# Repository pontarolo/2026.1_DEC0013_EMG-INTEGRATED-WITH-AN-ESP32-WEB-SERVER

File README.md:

<div align="center">

<h4 align="center">Electromyograph integrated with an ESP32 Web Server</h4>

</div>

<p align="center">
  <a href="#materials">Materials</a> •
  <a href="#diagrams">Diagrams</a> •
  <a href="software/README.md">Software</a> •
  <a href="LICENSE">License</a>
</p>

---

## Basic Overview

This project consists of an implementation of a circuit to measure specific muscle activity, consisting of two channels, which means that it is possible to measure two muscles simultaneously. The project emerges as a way to detect muscular issues and restraints in a low-cost and reliable manner. The general architecture of this project is a connection between the electromyograph PCB and the ESP32 microcontroller, where the ESP32 acts as a web server with an WebSocket to handle the data plotting. The GIF shown above was made from a video of the electromyograph in operation, which recorded the web page hosted by the ESP32.

## Goals

| Type | Goal |
| :--- | :--- |
| **Hardware** | Design a circuit that is capable of effectively measuring muscle voltage |
| **Hardware** | Make the circuit as noise-free as possible |
| **Software** | Write an optimized code that can display, in real time, the muscle data |

### Project Directory Structure

```text
├── hardware/             # PCB design files (symbols, footprints, models, and Gerbers)
│   ├── footprints/       # Custom component footprints (.kicad_mod)
│   ├── kicad_files/      # KiCad project files and manufacturing Gerbers
│   ├── models/           # 3D step files for components
│   └── symbols/          # Custom schematic symbol libraries (.kicad_sym)
├── images/               # Visual assets for documentation and tutorials
└── software/             # Firmware and source code for the project
    └── plot/             # ESP32 source code for data acquisition
```

## Description

This section explains the details of the project, including the materials and tools used, communication and electrical diagrams and examples of its functionality.

###  Materials

<table>
  <tr>
    <td align="center" valign="top" width="150" style="border: none;">
      <br>
      <strong>Resistor</strong><br>
      <font color="#666" size="2">2x 220Ω • 1/4 W • 5% • THT</font>
    </td>
    <td align="center" valign="top" width="150" style="border: none;">
      <br>
      <strong>Resistor</strong><br>
      <font color="#666" size="2">4x 100KΩ • 1/4 W • 5% • THT</font>
    </td>
    <td align="center" valign="top" width="150" style="border: none;">
      <br>
      <strong>Resistor</strong><br>
      <font color="#666" size="2">4x 220KΩ • 1/4 W • 5% • THT</font>
    </td>
    <td align="center" valign="top" width="150" style="border: none;">
      <br>
      <strong>Trimpot</strong><br>
      <font color="#666" size="2">1x 10KΩ • THT</font>
    </td>
  </tr>
  <tr>
    <td align="center" valign="top" width="150" style="border: none;">
      <br>
      <strong>Capacitor</strong><br>
      <font color="#666" size="2">2x 100μF • Electrolytic • THT</font>
    </td>
    <td align="center" valign="top" width="150" style="border: none;">
      <br>
      <strong>Capacitor</strong><br>
      <font color="#666" size="2">2x 220nF • Ceramic • THT</font>
    </td>
    <td align="center" valign="top" width="150" style="border: none;">
      <br>
      <strong>Battery</strong><br>
      <font color="#666" size="2">2x Lithium-Ion • 3.7V • 18650</font>
    </td>
    <td align="center" valign="top" width="150" style="border: none;">
      <br>
      <strong>MT3608</strong><br>
      <font color="#666" size="2">1x Module</font>
    </td>
  </tr>
  <tr>
    <td align="center" valign="top" width="150" style="border: none;">
      <br>
      <strong>TP4056</strong><br>
      <font color="#666" size="2">1x Module</font>
    </td>
    <td align="center" valign="top" width="150" style="border: none;">
      <br>
      <strong>LM324N</strong><br>
      <font color="#666" size="2">1x Integrated Circuit</font>
    </td>
    <td align="center" valign="top" width="150" style="border: none;">
      <br>
      <strong>TRRS Breakout</strong><br>
      <font color="#666" size="2">1x Module</font>
    </td>
    <td align="center" valign="top" width="150" style="border: none;">
      <br>
      <strong>ESP32</strong><br>
      <font color="#666" size="2">1x ESP-WROOM-32</font>
    </td>
  </tr>
  <tr>
    <td align="center" valign="top" width="150" style="border: none;">
      <br>
      <strong>Isopropanol</strong><br>
      <font color="#666" size="2">1x 99.8% Pure</font>
    </td>
    <td align="center" valign="top" width="150" style="border: none;">
      <br>
      <strong>Cell Holder</strong><br>
      <font color="#666" size="2">1x Lithium-Ion • 18650 • Single</font>
    </td>
    <td align="center" valign="top" width="150" style="border: none;">
      <br>
      <strong>EMG Cable</strong><br>
      <font color="#666" size="2">2x P2 Connection</font>
    </td>
    <td align="center" valign="top" width="150" style="border: none;">
      <br>
      <strong>Electrodes</strong><br>
      <font color="#666" size="2">6x Disposable</font>
    </td>
  </tr>
</table>

###  Communication Diagram

In this subsection we will discuss the communication diagram of the project to give a general view of the signal path and a clearer understanding of the circuit itself.

The image above represents the communication diagram, which shows the signal path throughout the whole project. The user's noisy low-voltage signal is sent to the printed circuit board (PCB) through silver $Ag$ or silver chloride $AgCl$ electrodes, where it can be properly filtered and amplified. Then the clean signal is carried to the ESP32 microcontroller that acts as a WebSocket Server to handle massive data plotting, hosting an HTML page that displays the graph.

---

###  Electrical Diagram

In this subsection we will discuss the communication diagram of the project to give a general view of the signal processing and a clearer understanding of the circuit itself.

The image above represents the electrical diagram, which shows the electrical connection between the components. As shown in the image, the circuit consists of:

| Component | Role in the circuit |
| :--- | :--- |
| **Resistors** | Set the gain stages, establish amplifier feedback loops, and stabilize signal lines. |
| **Trimpot** | Adjusts the virtual ground offset (reference voltage) to bias the EMG signal for the ESP32 ADC. |
| **Capacitors** | Filter out DC offsets (high-pass) and high-frequency noise (low-pass), and decouple power rails. |
| **Battery** | Provides clean, isolated 3.7V power to eliminate grid noise ($60\text{ Hz}$) and ensure user safety. |
| **MT3608** | Boosts the 3.7V battery to a stable 5V, ensuring full dynamic range for the op-amps. |
| **TP4056** | Handles safe Li-Ion battery charging and provides over-discharge protection. |
| **LM324N** | Handles differential amplification and active filtering of the microvolt-level muscle signals. |
| **TRRS Breakout** | Serves as the input jack for the 3-lead electrode cable (Signal +, Signal -, and Reference). |
| **ESP32 (Implicit)** | Samples the analog processed signal and hosts the WebSocket server for real-time live plotting. |

To secure the right voltage for the ESP32 ADC pins, a set of calculations were made, using the following equations:

- **Op-Amps:** By applying Kirchhoff's Laws, it is possible to obtain the expressions for Common and Differential Mode Gain:

| Name | Equation |
| :--- | :--- |
| **Common Mode Voltage** | $V_{cm} = \frac{V_{electrode(+)} + V_{electrode(-)}}{2}$ |
| **Common Mode Gain** | $A_{cm} = 1 - \frac{R_4}{Z_1}$ |
| **Differential Mode Voltage** | $V_{dif} = V_{electrode(+)} - V_{electrode(-)}$ |
| **Differential Mode Gain** | $A_{dif} = -\left(\frac{1}{2} + \frac{R_4}{R_5} + \frac{2R_4}{Z_3} + \frac{R_4}{2Z_1}\right)$ |

Where the complex impedances $Z_1$ and $Z_3$ are defined in the frequency domain ($s$-domain) as:

| Name | Equation |
| :--- | :--- |
| **Impedance $Z_1$** | $Z_1(s) = R_1 + \frac{1}{sC_1}$ |
| **Impedance $Z_3$** | $Z_3(s) = R_3 + \frac{1}{sC_2}$ |

By substituting the values, it follows that the circuit raises the muscle voltage by around $1000$ times.

- **Voltage Divider:** To reach a desired reference voltage, the following equation can be used:

| Name | Equation |
| :--- | :--- |
| **Reference Voltage** | $V_{out} = \left(5V\right)\left(\frac{R_{variable}}{R_{total}}\right)$ |

So, to adjust the center of the signal (reference), it is needed to setup the trimpot resistance to match the desired voltage.

---

### Pin Reference

For reference look at the <a href="#electrical">Electrical Diagram</a>.

| Pin Number | Connected to |
| :--- | :--- |
| **Pin 1** | VOUT_P (MT3608) |
| **Pin 2** | VOUT_N (MT3608) |
| **Pin 11** | O1 (Output 1) |
| **Pin 12** | O2 (Output 2) |

All the others are **disconnected**.

> [!IMPORTANT]  
> Even though the project has only one graph, both of the outputs needs to be connected. The first output (O1) is the main channel, and the second output (O2) is an auxiliar channel that helps in cleaning the noise.

---

## Prototype

A single-channel prototype was implemented on a breadboard to validate the circuit's functionality during the testing phase. The prototype can be seen in the image below.

---

## Final Assembly and PCB Layout

In the images below, it is shown the final assembly, consisting of two main blocks, the printed circuit board (PCB), which was ordered from <a href="https://jlcpcb.com/">JLCPCB</a>, and the ESP32 microcontroller, and the printed circuit board (PCB) layout.

> [!TIP]
> In environments highly susceptible to noise, such as an electromyograph, it is important to clean the board with isopropanol and an anti-static brush to remove any soldering residue.

To help reduce the noise, it was used copper pouring in both layers of the printed circuit board (PCB). In the table below it is presented some important parameters of the board.

| Parameter | Value |
| :--- | :--- |
| **Power Trace Width** | $0.4 \ mm$ |
| **Signal Trace Width** | $0.2 \ mm$ |
| **Clearance** | $0.2 \ mm$ |
| **Via Size** | $0.6 \ mm$ |
| **Via Hole** | $0.3 \ mm$ |
| **μVia Size** | $0.3 \ mm$ |
| **μVia Hole** | $0.1 \ mm$ |
| **DP Width** | $0.2 \ mm$ |
| **DP Gap** | $0.25 \ mm$ |

---

## Electrode Placement

| Cable End | Role |
| :--- | :--- |
| **Yellow** | Reference |
| **Green** | Negative |
| **Red** | Positive |

> [!IMPORTANT]  
> Place the yellow electrode in a non-muscular part of the body, and the centers of green and red electrodes within 2 centimeters apart along the desired muscle fibers.

---

## Software Used

To install the software, click on the name and you will be redirected to the download page. 

<table>
  <tr>
    <td align="center" valign="top" width="120" style="border: none;">
      <br>
      <strong><a href="https://www.arduino.cc/en/software/">Arduino IDE</a></strong><br>
      <font color="#666" size="2">v2.3.8</font>
    </td>
        <td align="center" valign="top" width="120" style="border: none;">
      <br>
      <strong><a href="https://www.kicad.org/download/">KiCad</a></strong><br>
      <font color="#666" size="2">v10.0.2</font>
    </td>
     </td>
        <td align="center" valign="top" width="120" style="border: none;">
      <br>
      <strong><a href="https://krita.org/pt-br/download/">Krita</a></strong><br>
      <font color="#666" size="2">v6.0.2.1</font>
    </td>
  </tr>
</table>

## References

[1] Rodrigues, I. T., Bonfim, M. J., Miyazaki, D. R., da Fonseca, M. S. R. S., & da Silva Ferraz, R. Dispositivo de Aquisição de Sinais Eletromiograficos de Superfície para Monitoramento em Tempo Real.

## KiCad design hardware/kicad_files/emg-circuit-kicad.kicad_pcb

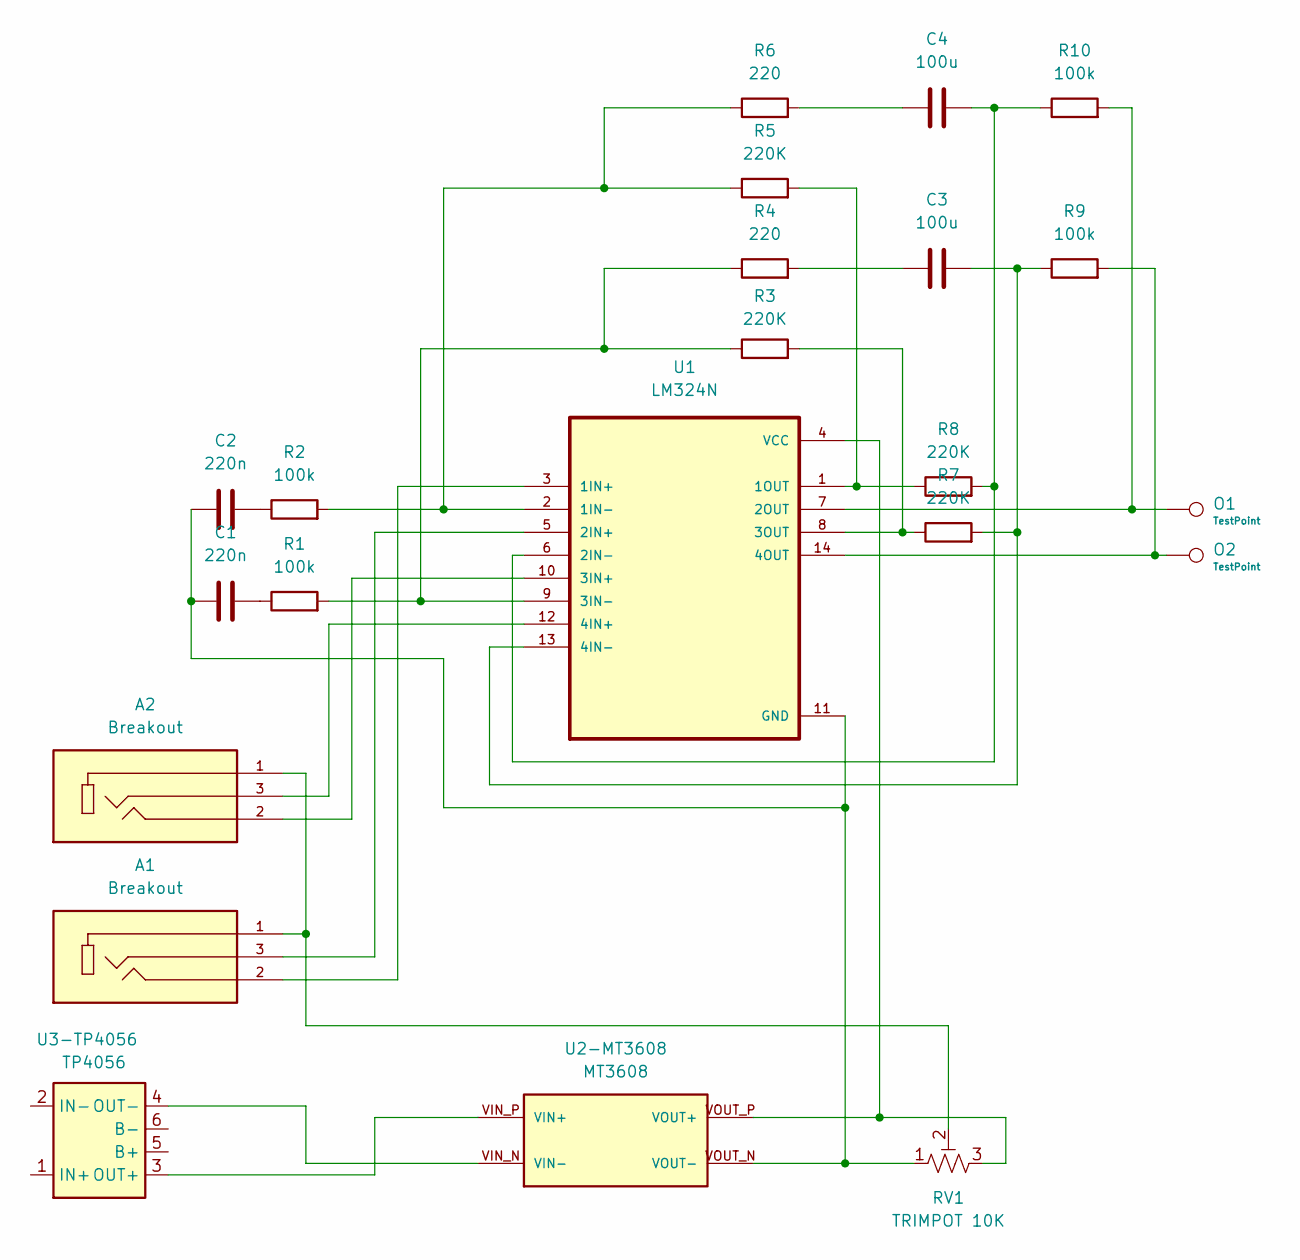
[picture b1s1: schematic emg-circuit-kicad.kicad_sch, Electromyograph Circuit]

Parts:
A1, A2: Breakout; breakout; PARTREV 1.01
C1, C2: 220n; capacitor_220n
C3, C4: 100u; capacitor_100u
O1, O2: TestPoint; TestPoint_THTPad_1.5x1.5mm_Drill0.7mm
R1, R2, R9, R10: 100k; resistor
R3, R5, R7, R8: 220K; resistor
R4, R6: 220; resistor
RV1: TRIMPOT 10K; trimpot
U1: LM324N; lm324
U2-MT3608: MT3608; mt3608
U3-TP4056: TP4056; tp4056

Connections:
unnamed: A1.1, A2.1, RV1.2
unnamed: C1.2, R1.1
unnamed: C2.2, R2.1
unnamed: C3.1, R4.2
unnamed: C4.1, R6.2
unnamed: A1.2, U1.3 (1IN+)
unnamed: R2.2, R5.1, R6.1, U1.2 (1IN-)
unnamed: R5.2, R8.1, U1.1 (1OUT)
unnamed: A1.3, U1.5 (2IN+)
unnamed: C4.2, R8.2, R10.1, U1.6 (2IN-)
unnamed: O1.1 (1_1), R10.2, U1.7 (2OUT)
unnamed: A2.2, U1.10 (3IN+)
unnamed: R1.2, R3.1, R4.1, U1.9 (3IN-)
unnamed: R3.2, R7.1, U1.8 (3OUT)
unnamed: A2.3, U1.12 (4IN+)
unnamed: C3.2, R7.2, R9.1, U1.13 (4IN-)
unnamed: O2.1 (1_1), R9.2, U1.14 (4OUT)
unnamed: C1.1, C2.1, RV1.1, U1.11 (GND), U2-MT3608.VOUT_N (VOUT-)
unnamed: RV1.3, U1.4 (VCC), U2-MT3608.VOUT_P (VOUT+)
unnamed: U2-MT3608.VIN_P (VIN+), U3-TP4056.3 (OUT+)
unnamed: U2-MT3608.VIN_N (VIN-), U3-TP4056.4 (OUT-)

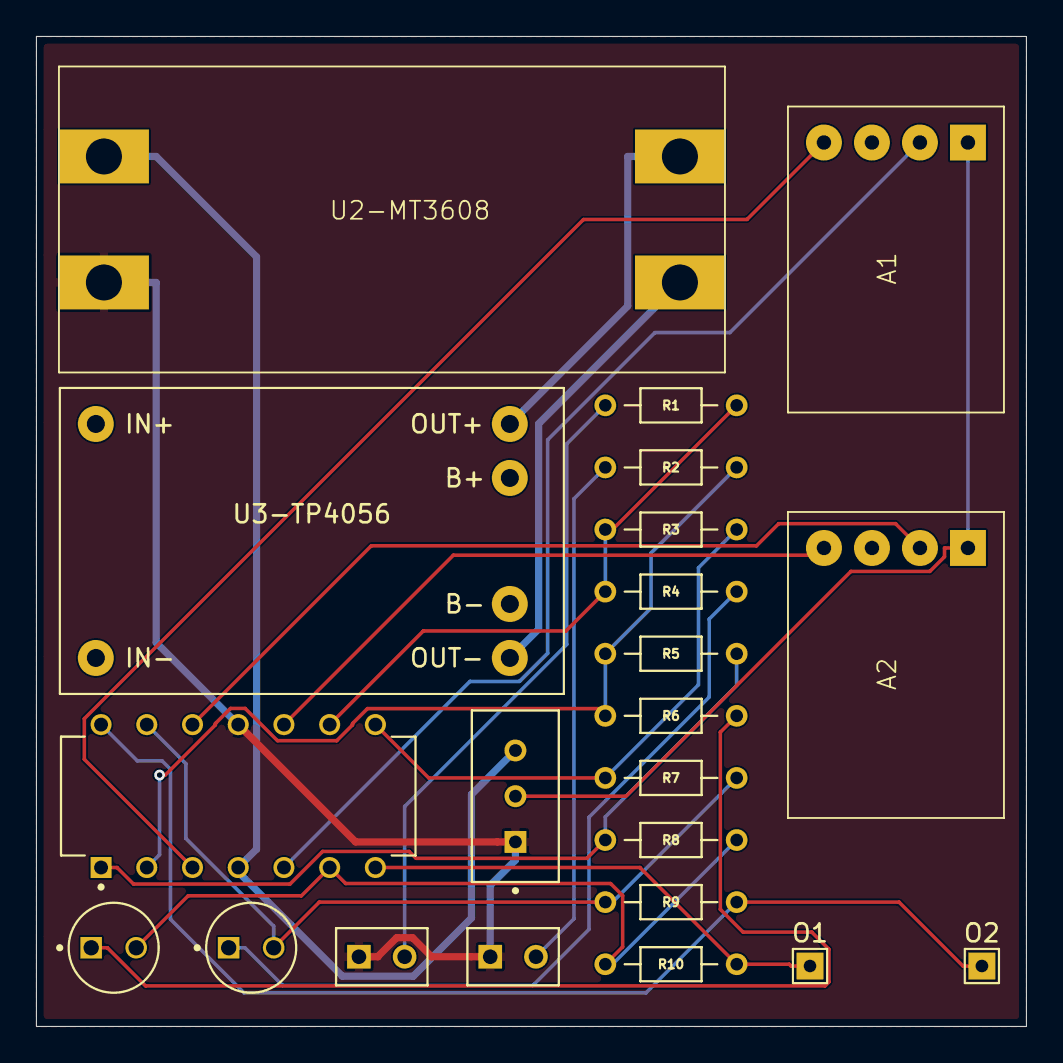
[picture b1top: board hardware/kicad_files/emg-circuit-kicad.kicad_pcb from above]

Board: 2 copper layers, 55.0 x 55.0 mm, 22 parts (0 on the bottom side), 21 nets.

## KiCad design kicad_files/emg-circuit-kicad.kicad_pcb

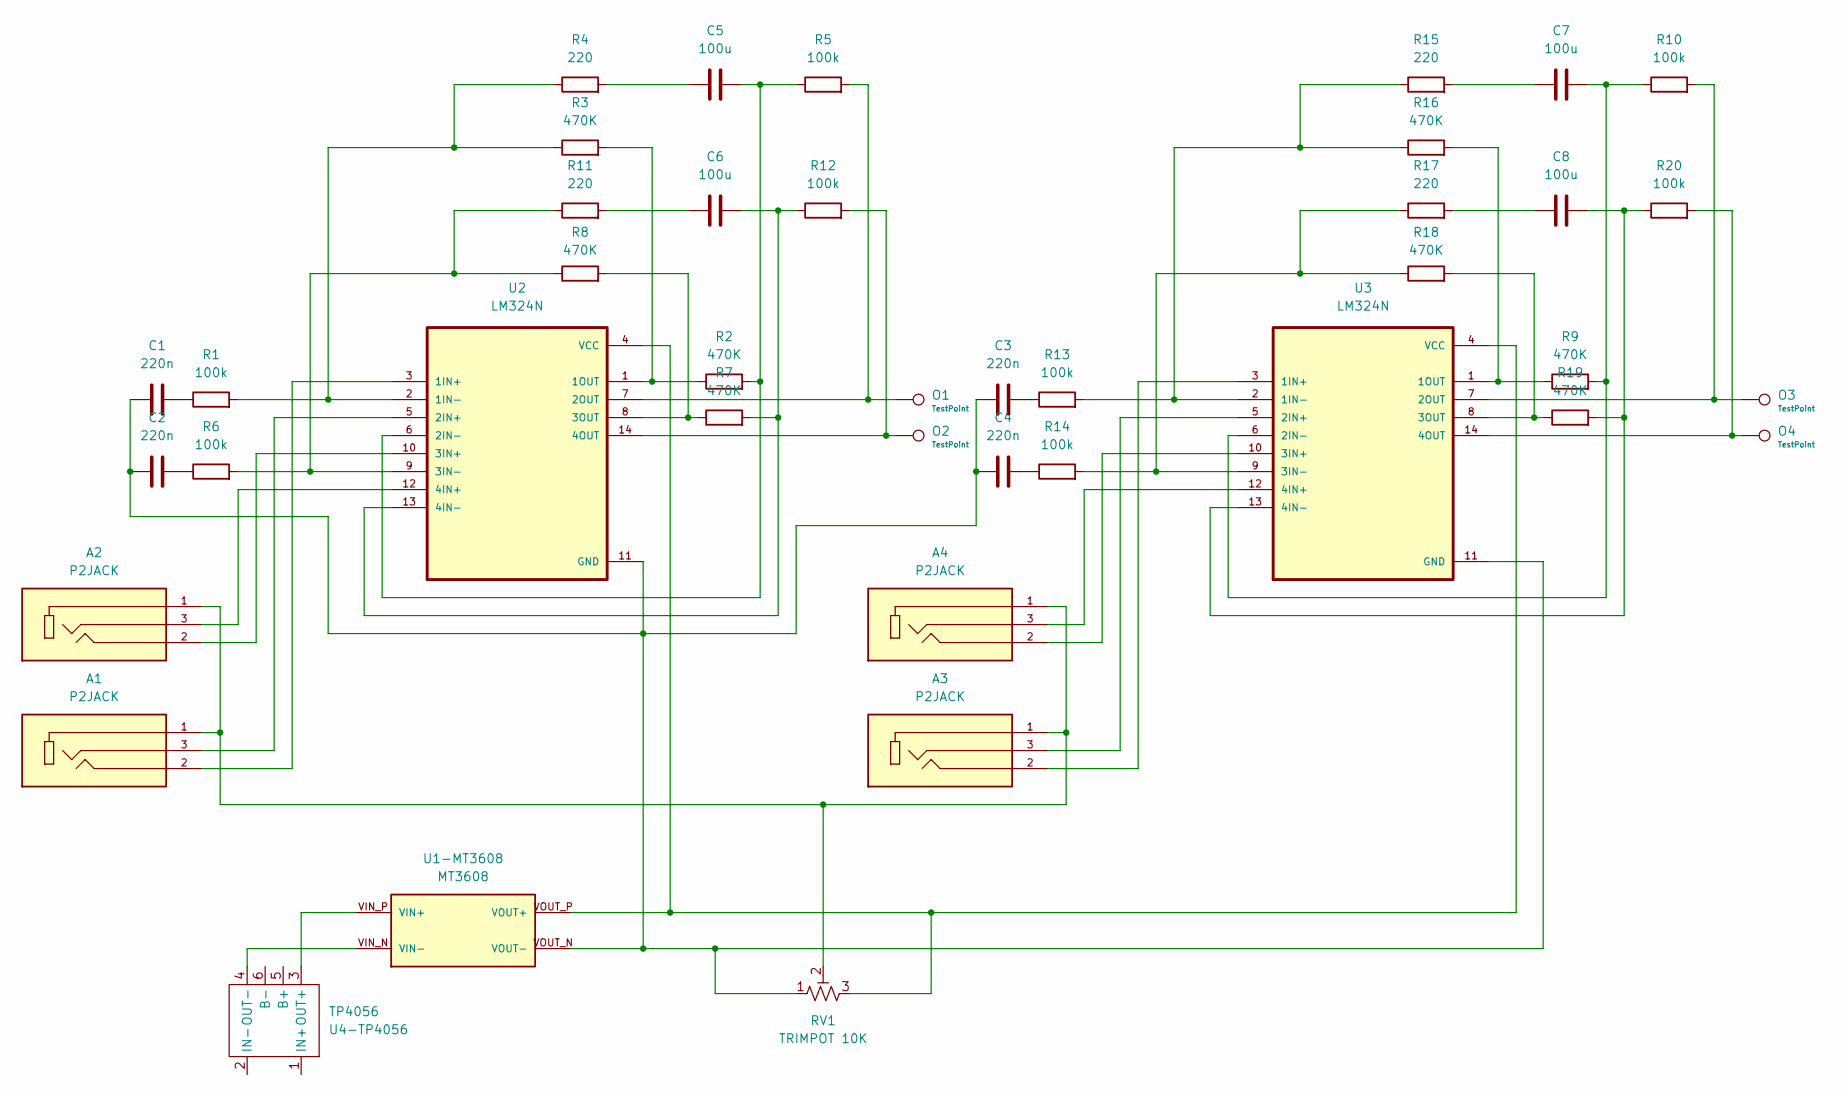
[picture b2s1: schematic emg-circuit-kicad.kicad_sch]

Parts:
A1, A2, A3, A4: P2JACK; p2jack; PARTREV 1.01
C1, C2, C3, C4: 220n; capacitor_220n
C5, C6, C7, C8: 100u; capacitor_100u
O1, O2, O3, O4: TestPoint; TestPoint_THTPad_1.5x1.5mm_Drill0.7mm
R1, R5, R6, R10, R12, R13, R14, R20: 100k; resistor
R2, R3, R7, R8, R9, R16, R18, R19: 470K; resistor
R4, R11, R15, R17: 220; resistor
RV1: TRIMPOT 10K; trimpot
U1-MT3608: MT3608; mt3608
U2, U3: LM324N; lm324
U4-TP4056: TP4056; tp4056

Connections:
unnamed: A1.1, A2.1, A3.1, A4.1, RV1.2
unnamed: C1.2, R1.1
unnamed: C2.2, R6.1
unnamed: C3.2, R13.1
unnamed: C4.2, R14.1
unnamed: C5.1, R4.2
unnamed: C6.1, R11.2
unnamed: C7.1, R15.2
unnamed: C8.1, R17.2
unnamed: U1-MT3608.VIN_P (VIN+), U4-TP4056.3 (OUT+)
unnamed: U1-MT3608.VIN_N (VIN-), U4-TP4056.4 (OUT-)
unnamed: RV1.3, U1-MT3608.VOUT_P (VOUT+), U2.4 (VCC), U3.4 (VCC)
unnamed: C1.1, C2.1, C3.1, C4.1, RV1.1, U1-MT3608.VOUT_N (VOUT-), U2.11 (GND), U3.11 (GND)
unnamed: A1.2, U2.3 (1IN+)
unnamed: R1.2, R3.1, R4.1, U2.2 (1IN-)
unnamed: R2.1, R3.2, U2.1 (1OUT)
unnamed: A1.3, U2.5 (2IN+)
unnamed: C5.2, R2.2, R5.1, U2.6 (2IN-)
unnamed: O1.1 (1_1), R5.2, U2.7 (2OUT)
unnamed: A2.2, U2.10 (3IN+)
unnamed: R6.2, R8.1, R11.1, U2.9 (3IN-)
unnamed: R7.1, R8.2, U2.8 (3OUT)
unnamed: A2.3, U2.12 (4IN+)
unnamed: C6.2, R7.2, R12.1, U2.13 (4IN-)
unnamed: O2.1 (1_1), R12.2, U2.14 (4OUT)
unnamed: A3.2, U3.3 (1IN+)
unnamed: R13.2, R15.1, R16.1, U3.2 (1IN-)
unnamed: R9.1, R16.2, U3.1 (1OUT)
unnamed: A3.3, U3.5 (2IN+)
unnamed: C7.2, R9.2, R10.1, U3.6 (2IN-)
unnamed: O3.1 (1_1), R10.2, U3.7 (2OUT)
unnamed: A4.2, U3.10 (3IN+)
unnamed: R14.2, R17.1, R18.1, U3.9 (3IN-)
unnamed: R18.2, R19.1, U3.8 (3OUT)
unnamed: A4.3, U3.12 (4IN+)
unnamed: C8.2, R19.2, R20.1, U3.13 (4IN-)
unnamed: O4.1 (1_1), R20.2, U3.14 (4OUT)

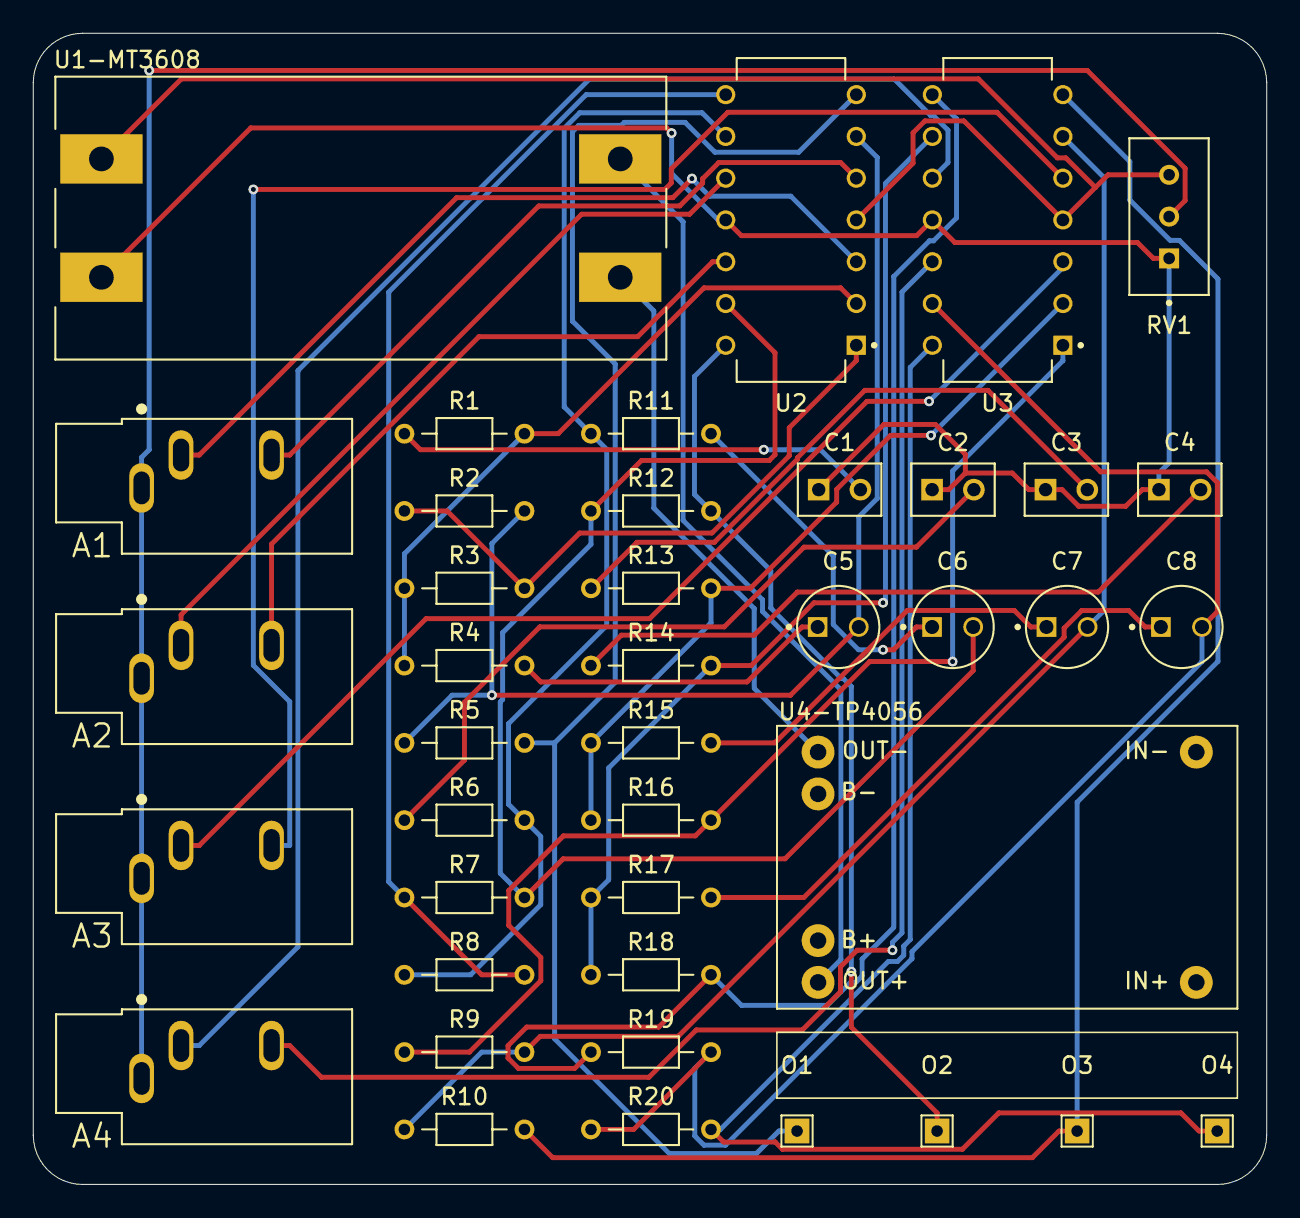
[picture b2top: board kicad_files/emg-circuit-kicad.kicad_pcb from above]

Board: 2 copper layers, 75.0 x 70.0 mm, 41 parts (0 on the bottom side), 37 nets.

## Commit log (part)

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2026-05-23 chore: init
2026-05-23 docs: update README
2026-05-28 perf: optimize the code
2026-06-26 docs: add code explanation
2026-06-26 docs: change materials list
2026-06-26 docs: add pin reference
2026-06-26 docs: fix a typo
2026-06-26 docs: add software banner
2026-06-26 docs: add goals section
2026-06-26 docs: add krita as software used
2026-06-26 docs: update resistors specifications
2026-06-28 docs: add pcb layout
2026-06-28 docs: move pcb layout
2026-06-28 docs: remove pcb layout

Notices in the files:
README.md:
License: MIT
hardware/kicad_files/emg-circuit-kicad.kicad_sch:
Released under the MIT License (MIT)
